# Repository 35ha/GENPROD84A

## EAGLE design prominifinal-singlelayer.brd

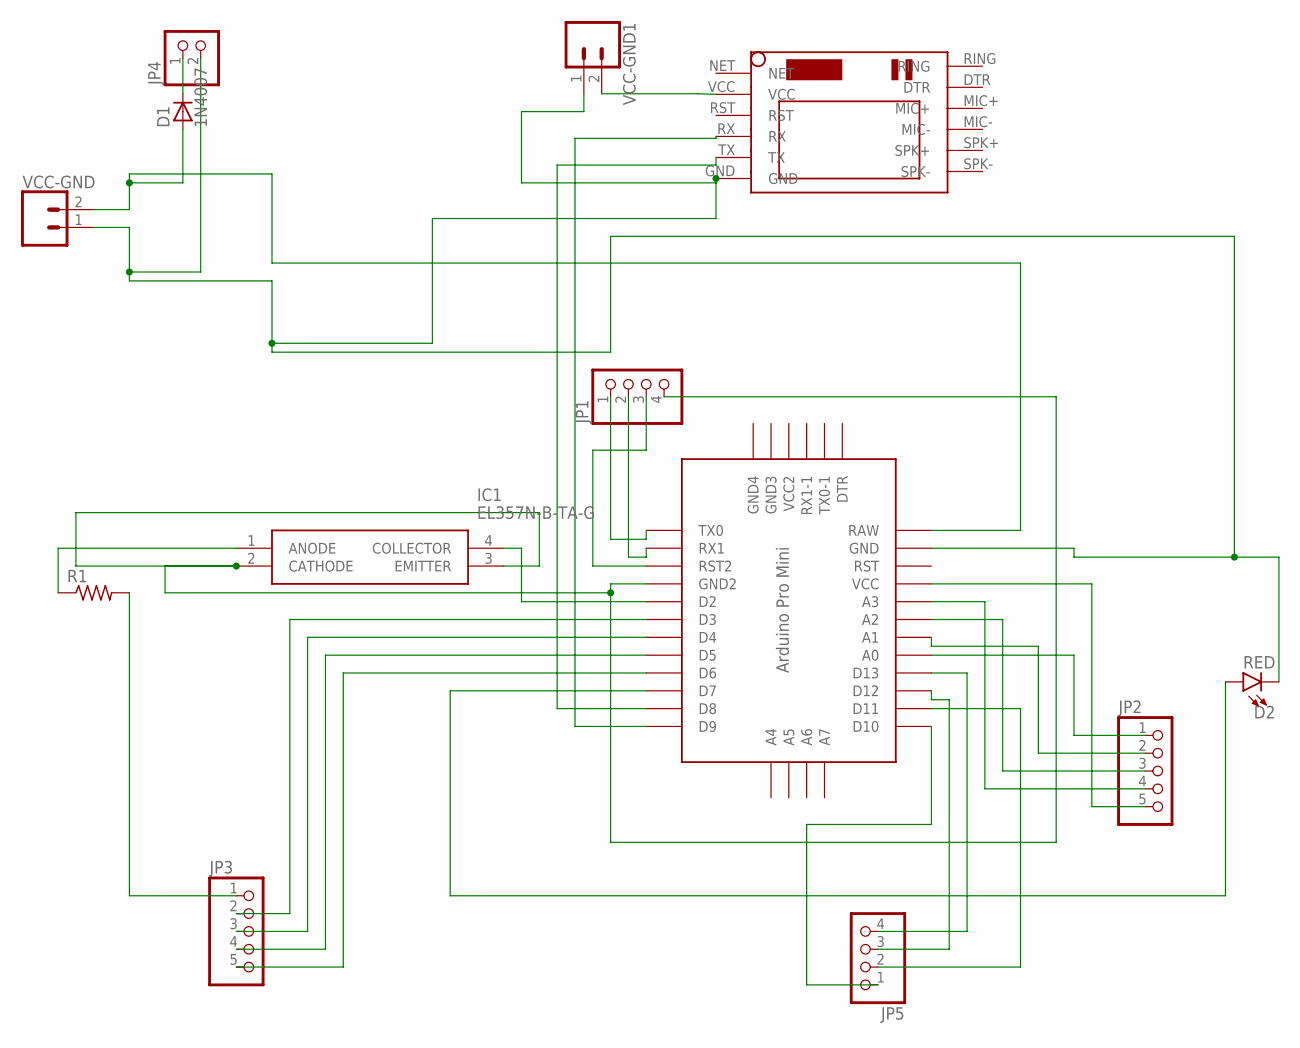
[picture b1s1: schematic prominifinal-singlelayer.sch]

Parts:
D1: 1N4007; SMA
D2: RED; LED-1206
IC1: EL357N-B-TA-G; SOP254P700X200-4N
JP1, JP5: PINHD-1X4; 1X04
JP2, JP3: PINHD-1X5; 1X05
JP4: PINHD-1X2; 1X02
PROMINI: PRO-MINI
R1: R-US_R1206; R1206
U$1: SIM800LMODULE
VCC-GND, VCC-GND1: CONN_025MM; SCREWTERMINAL-5MM-2

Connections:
unnamed: D1.A, PROMINI.RAW, VCC-GND.2
unnamed: JP1.1, PROMINI.TX0
unnamed: IC1.2 (CATHODE), IC1.3 (EMITTER), JP1.4, PROMINI.GND1 (GND2)
unnamed: JP2.1, PROMINI.A0
unnamed: IC1.4 (COLLECTOR), PROMINI.D2
unnamed: PROMINI.D9, U$1.RX
unnamed: D2.A, PROMINI.D7
unnamed: JP3.1, R1.2
unnamed: JP3.2, PROMINI.D3
unnamed: JP3.3, PROMINI.D4
unnamed: JP5.4, PROMINI.D13
unnamed: JP3.5, PROMINI.D6
unnamed: JP2.2, PROMINI.A1
unnamed: JP1.2, PROMINI.RX1
unnamed: PROMINI.D8, U$1.TX
unnamed: JP2.3, PROMINI.A2
unnamed: JP2.4, PROMINI.A3
unnamed: JP1.3, PROMINI.RST1 (RST2)
unnamed: D2.C, JP4.2, PROMINI.GND, U$1.GND, VCC-GND.1, VCC-GND1.1
unnamed: U$1.VCC, VCC-GND1.2
unnamed: JP2.5, PROMINI.VCC
unnamed: JP3.4, PROMINI.D5
unnamed: JP5.3, PROMINI.D12
unnamed: IC1.1 (ANODE), R1.1
unnamed: JP5.2, PROMINI.D11
unnamed: JP5.1, PROMINI.D10
unnamed: D1.K (C), JP4.1

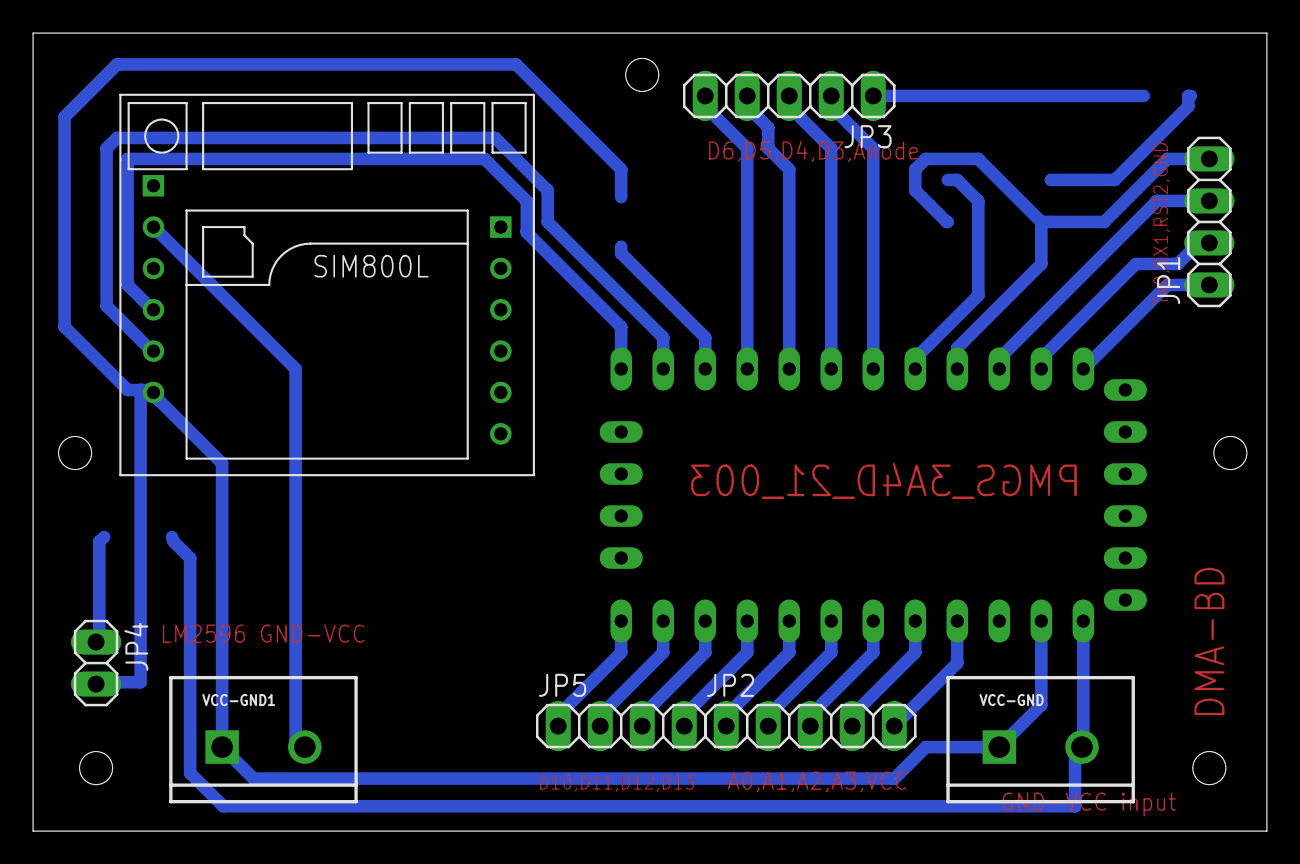
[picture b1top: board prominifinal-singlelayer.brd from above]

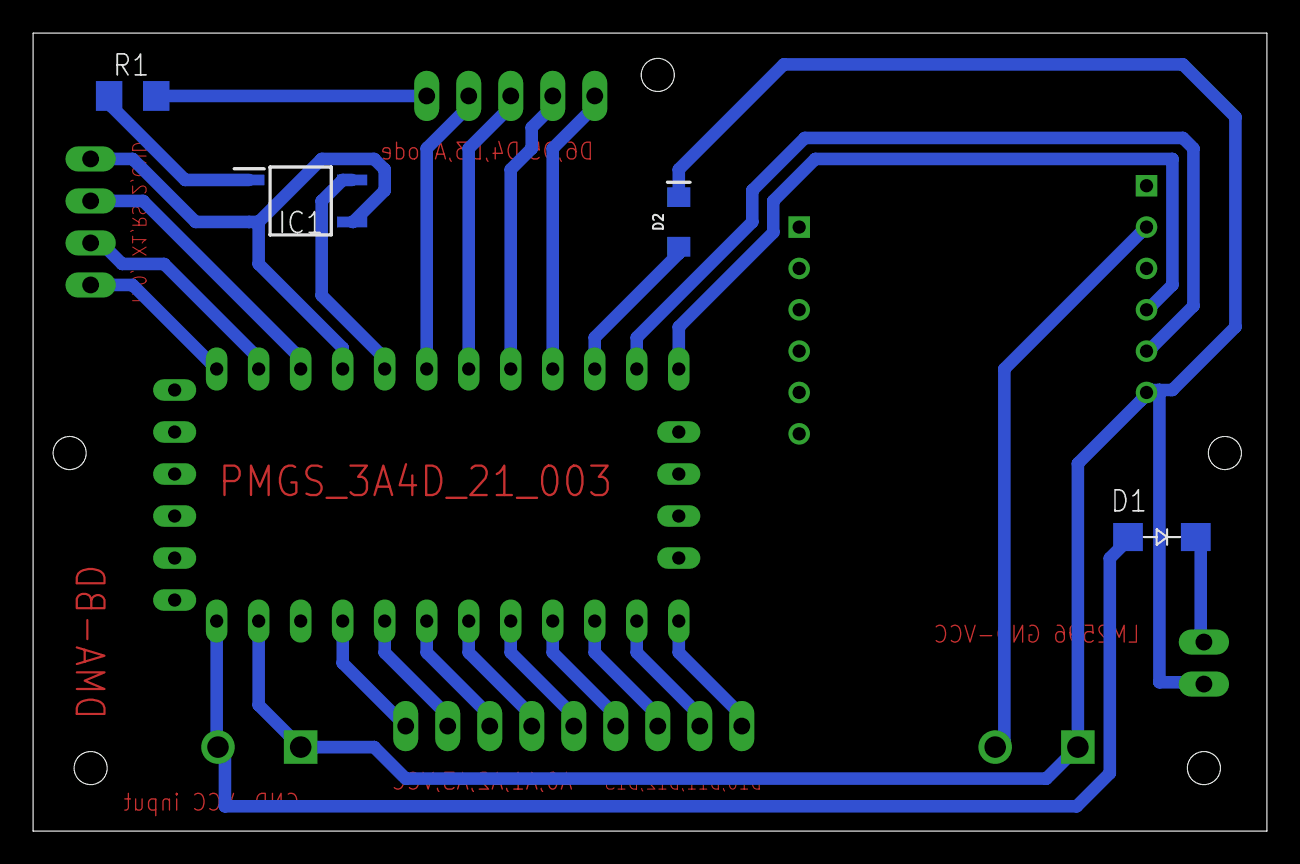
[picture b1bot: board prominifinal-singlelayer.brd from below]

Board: 2 copper layers, 74.6 x 48.2 mm, 13 parts (4 on the bottom side), 27 nets.

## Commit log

2021-02-15 added all files

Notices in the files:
parts and their libraries:
SparkFun-LED: Licensing: Creative Commons ShareAlike 4.0 International - https://creativecommons.org/licenses/by-sa/4.0
